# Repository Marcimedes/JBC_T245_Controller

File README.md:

# JBC_T245_Controller
JBC T245 Controller

Mounting Holes:
2.1 mm dia.
64mm x 74mm 

Board:
71mm x 80mm

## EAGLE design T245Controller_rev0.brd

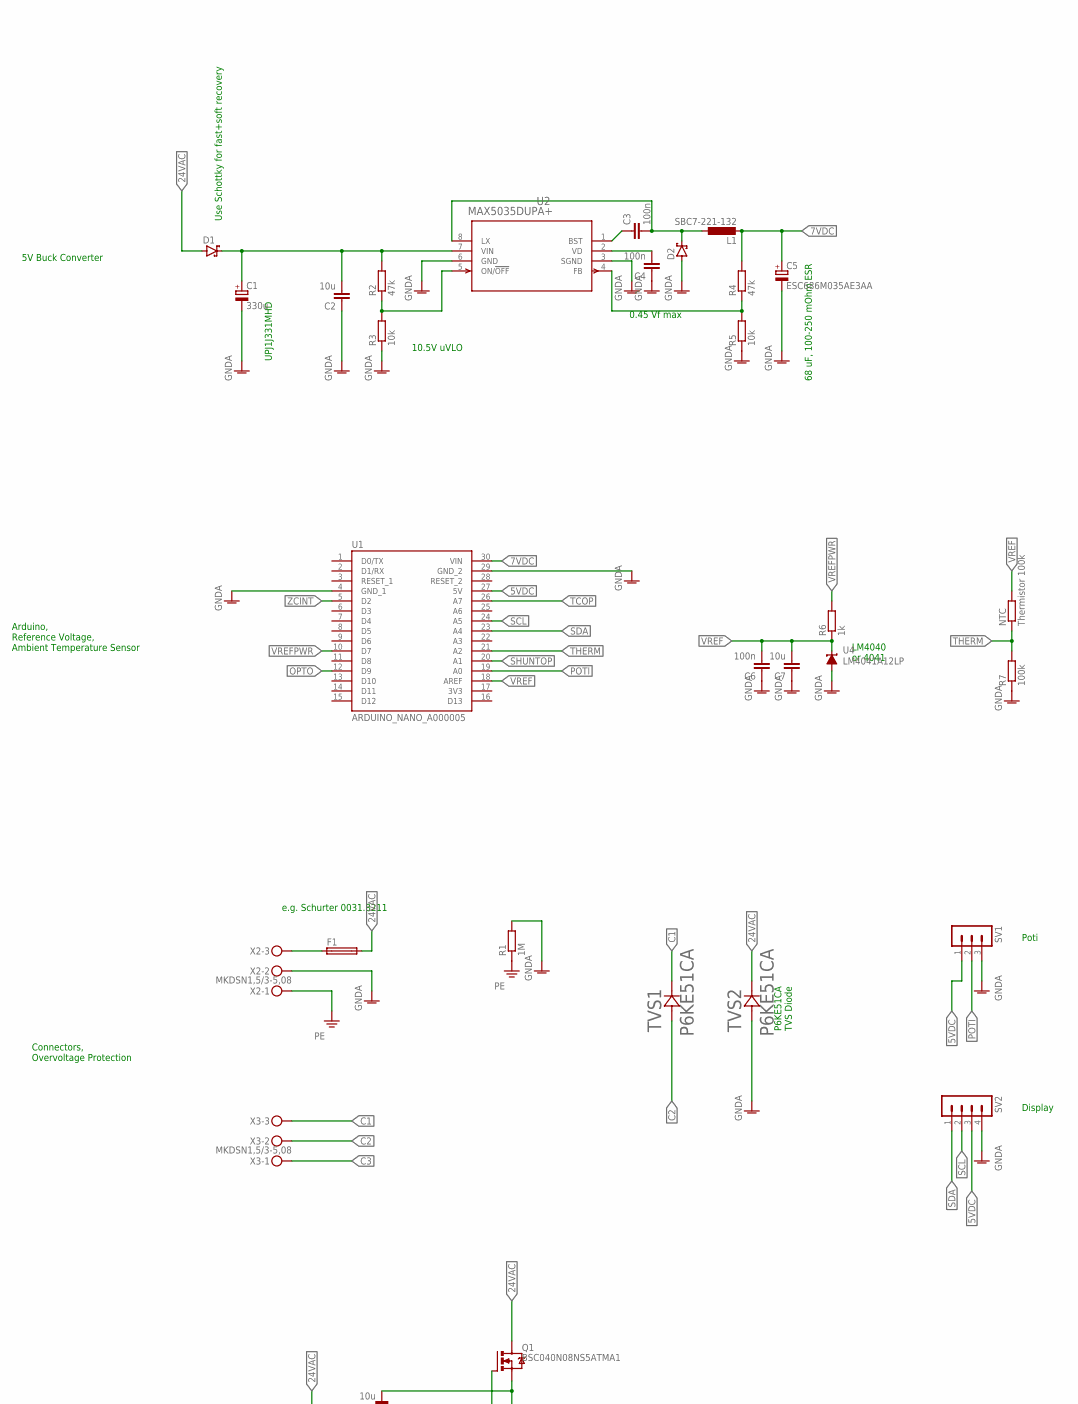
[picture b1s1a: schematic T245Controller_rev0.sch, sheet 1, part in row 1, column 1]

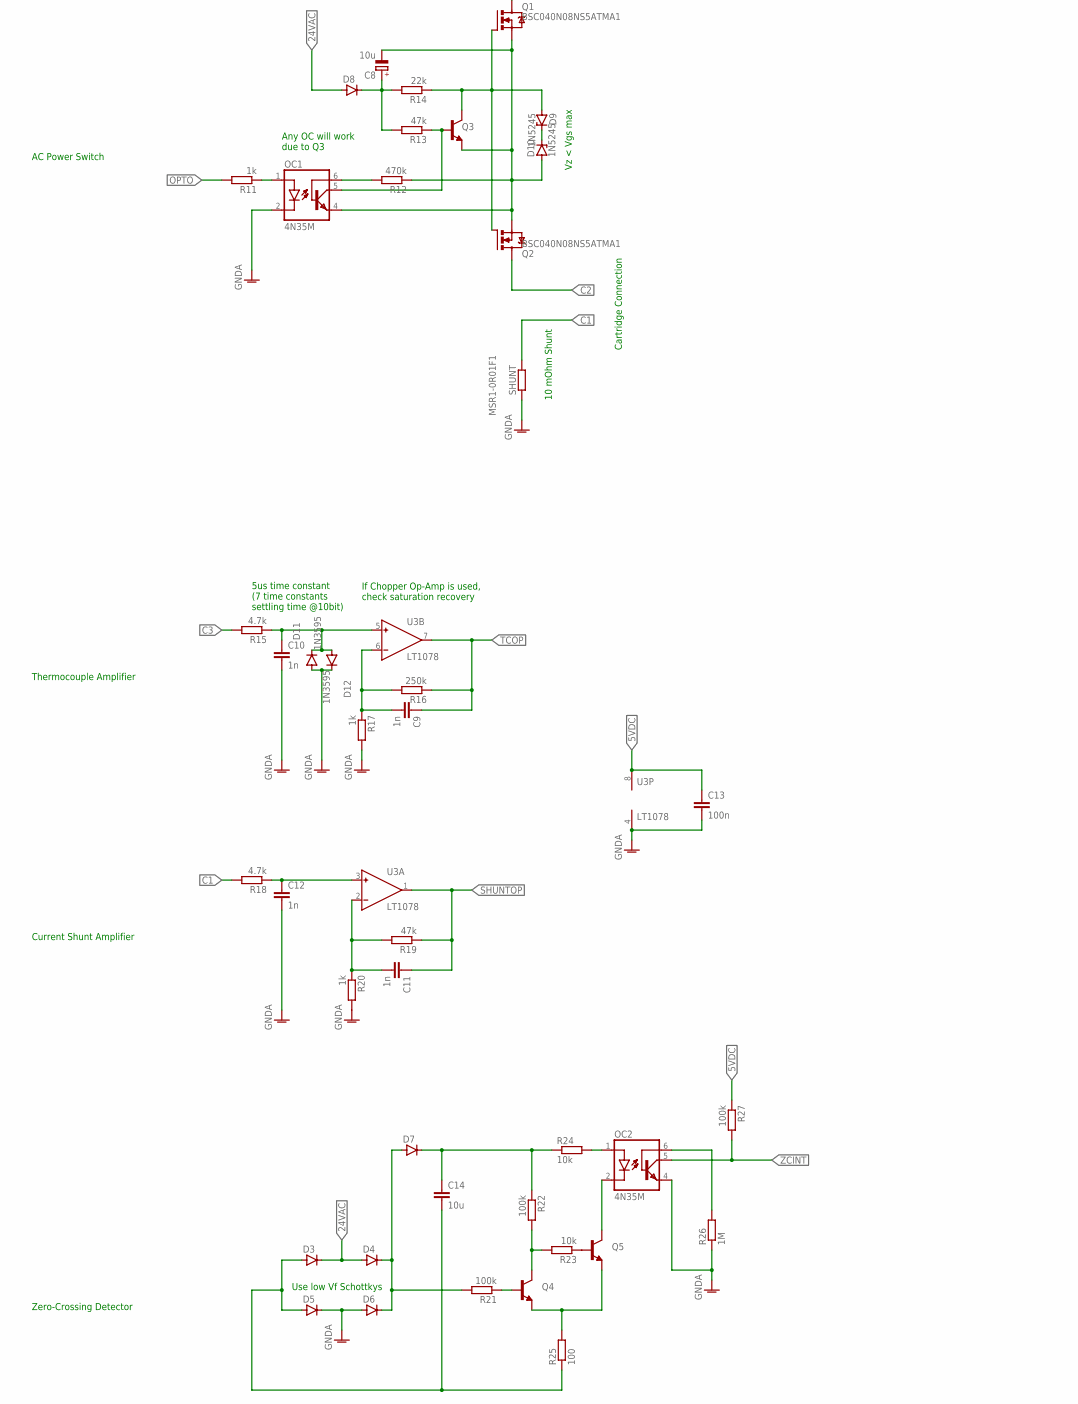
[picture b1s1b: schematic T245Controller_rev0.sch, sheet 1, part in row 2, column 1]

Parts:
C1: 330u; E5-13
C2, C7, C14: 10u; C050-024X044
C3, C4, C6, C13: 100n; C050-024X044
C5: ESC686M035AE3AA; E2,5-6
C8: 10u; E2,5-6
C9, C10, C11, C12: 1n; C050-024X044
D1, D2: SCHOTTKY-DIODEF126Z12; F126Z12
D3, D4, D5, D6, D7, D8: DIODE-D-7.5; D-7.5
D9, D10: 1N5245; DO41Z10
D11, D12: 1N3595; D-7.5
F1: SH22,5A
L1: SBC7-221-132; 0207/10
NTC: Thermistor 100k; 0207/10
OC1, OC2: 4N35M; DIL06
Q1, Q2: BSC040N08NS5ATMA1; TO220BV
Q3, Q4, Q5: 2N5550-NPN-TO92-EBC; TO92-EBC
R1, R26: 1M; 0207/10
R2, R4, R13, R19: 47k; 0207/10
R3, R5, R23, R24: 10k; 0207/10
R6, R11, R17, R20: 1k; 0207/10
R7, R21, R22, R27: 100k; 0207/10
R12: 470k; 0207/10
R14: 22k; 0207/10
R15, R18: 4.7k; 0207/10
R16: 250k; 0207/10
R25: 100; 0207/10
SHUNT: MSR1-0R01F1; 0207/12
SV1: MA03-1
SV2: MA04-1
TVS1, TVS2: P6KE51CA; P6KESERIES_LTF
U1: ARDUINO_NANO_A000005; MODULE_A000005
U2: MAX5035DUPA+; 21-0043_P8+3_MXM
U3: LT1078; DIL08
U4: LM4041A12LP; LP_O-PBCY-W3
X2, X3: MKDSN1,5/3-5,08

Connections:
3V3: U1.17 (3V3)
5VDC: C13.1, R27.1, SV1.1, SV2.3, U1.27 (5V), U3.8 (V+)
7VDC: C5.+, L1.2, R4.2, U1.30 (VIN)
24VAC: D1.A, D3.C, D4.A, D8.A, F1.2, Q1.D, TVS2.1 (11)
C1: R18.2, SHUNT.2, TVS1.1 (11), X3.3
C2: Q2.D, TVS1.2 (12), X3.2
C3: R15.2, X3.1
GNDA: C1.-, C2.1, C4.1, C5.-, C6.1, C7.1, C10.2, C12.2, C13.2, D2.A, D5.C, D6.A, D11.A, D12.C, OC1.2 (C), OC2.4 (EMI), R1.2, R3.1, R5.1, R7.1, R17.2, R20.2, R26.1, SHUNT.1, SV1.3, SV2.4, TVS2.2 (12), U1.4 (GND_1), U1.29 (GND_2), U2.3 (SGND), U2.6 (GND), U3.4 (V-), U4.3 (A), X2.2
unnamed: C9.2, R16.2, R17.1, U3.6 (IN-)
unnamed: OC1.1 (A), R11.1
unnamed: D9.A, Q1.G, Q2.G, Q3.C, R14.1
unnamed: C8.-, D10.A, OC1.4 (EMI), Q1.S, Q2.S, Q3.E, R12.1
unnamed: OC1.6 (BAS), R12.2
unnamed: Q5.B, R23.1
unnamed: R4.1, R5.2, U2.4 (FB)
unnamed: C3.2, D2.C, L1.1, U2.8 (LX)
unnamed: C8.+, D8.C, R13.2, R14.2
unnamed: C1.+, C2.2, D1.C, R2.2, U2.7 (VIN)
unnamed: C10.1, D11.C, D12.A, R15.1, U3.5 (IN+)
unnamed: C3.1, U2.1 (BST)
unnamed: OC1.5 (COL), Q3.B, R13.1
unnamed: D9.C, D10.C
unnamed: R2.1, R3.2, U2.5 (ON/!OFF)
unnamed: C4.2, U2.2 (VD)
unnamed: C14.2, D3.A, D5.A, R25.1
unnamed: OC2.6 (BAS), R26.2
unnamed: F1.1, X2.3
unnamed: C12.1, R18.1, U3.3 (IN+)
unnamed: D4.C, D6.C, D7.A, R21.2
unnamed: C11.2, R19.2, R20.1, U3.2 (IN-)
unnamed: Q4.B, R21.1
unnamed: C14.1, D7.C, R22.1, R24.1
unnamed: Q4.C, R22.2, R23.2
unnamed: Q4.E, Q5.E, R25.2
unnamed: OC2.1 (A), R24.2
unnamed: OC2.2 (C), Q5.C
OPTO: R11.2, U1.12 (D9)
PE: R1.1, X2.1
POTI: SV1.2, U1.19 (A0)
SCL: SV2.2, U1.24 (A5)
SDA: SV2.1, U1.23 (A4)
SHUNTOP: C11.1, R19.1, U1.20 (A1), U3.1 (OUT)
TCOP: C9.1, R16.1, U1.26 (A7), U3.7 (OUT)
THERM: NTC.1, R7.2, U1.21 (A2)
VREF: C6.2, C7.2, NTC.2, R6.1, U1.18 (AREF), U4.2 (C)
VREFPWR: R6.2, U1.10 (D7)
ZCINT: OC2.5 (COL), R27.2, U1.5 (D2)

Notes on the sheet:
Use Schottky for fast+soft recovery
Any OC will work due to Q3
5us time constant (7 time constants settling time @10bit)
Vz < Vgs max
0.45 Vf max
10.5V uVLO
UPJ1J331MHD
68 uF, 100-250 mOhm ESR
e.g. Schurter 0031.8211
LM4040 or 4041
If Chopper Op-Amp is used, check saturation recovery
10 mOhm Shunt
Cartridge Connection
Zero-Crossing Detector
Current Shunt Amplifier
Thermocouple Amplifier
AC Power Switch
Connectors, Overvoltage Protection
Arduino, Reference Voltage, Ambient Temperature Sensor
5V Buck Converter
P6KE51CA TVS Diode
Use low Vf Schottkys
Poti
Display

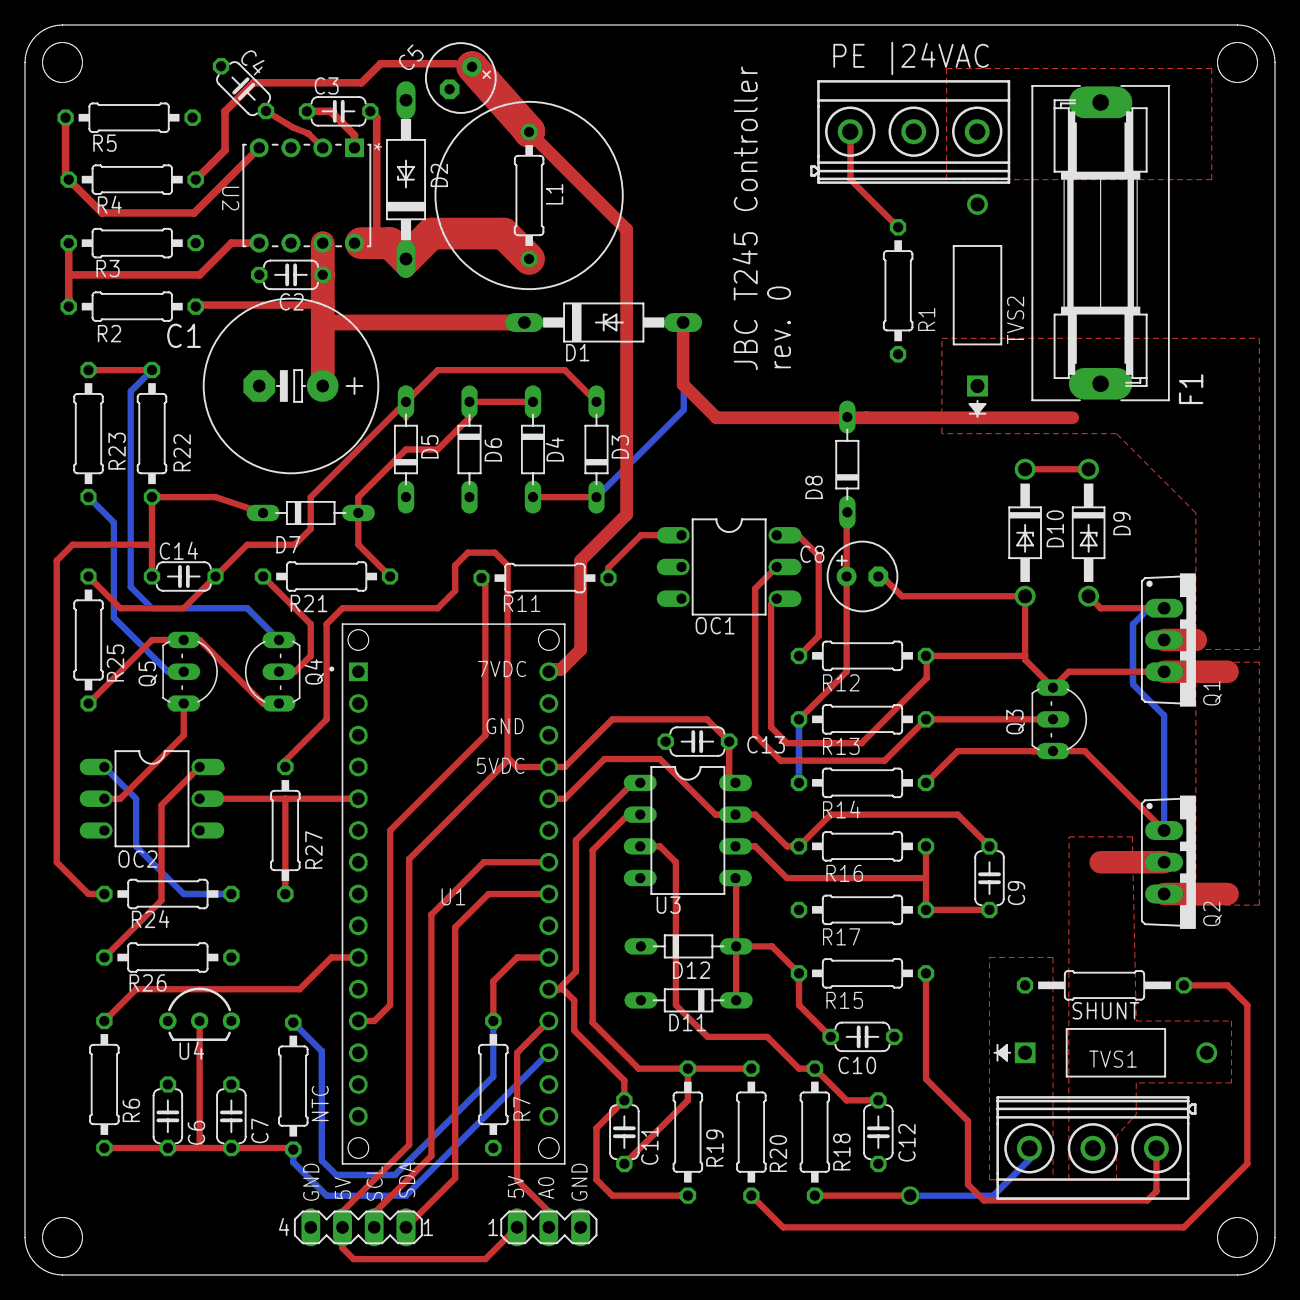
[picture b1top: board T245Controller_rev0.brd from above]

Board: 2 copper layers, 100.0 x 100.0 mm, 71 parts (0 on the bottom side), 46 nets.

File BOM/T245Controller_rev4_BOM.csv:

,T245 (24 VAC),,,
,,,,
Part,Nominal Value,Example Part,Description,Approx. Price
C1,470uF 50V,Nichicon UHE1H471MHD3,"DC-DC input cap, impedance < 80 mOhms @100kHz",1.30 
C2,1uF 100V,FG24X7S2A105KRT06,"DC-DC input cap, MLCC",0.60 
C3,100nF 100V,SR211C104KARTR1,DC-DC cap,0.20 
C4,100nF 100V,SR211C104KARTR1,DC-DC cap,0.20 
C5,68uF 16V,Nichicon UHV1V680MED,"DC-DC output cap, impedance 100-200 mOhms @100kHz",0.40 
C6,100nF 16V,SR211C104KARTR1,Voltage Reference cap,0.20 
C7,10uF 10V,FG14X7R1A106KRT06 ,Voltage Reference cap,0.50 
C8,47uF 50V,Rubycon 50YXJ47M6.3X11,Villard Circuit cap,0.30 
C9,"1nF, 16V",Vishay K102K10X7RH5UH5,Opamp loop cap,0.10 
C10,"1nF, 16V",Vishay K102K10X7RH5UH5,Amplifier input lowpass cap,0.10 
C11,"1nF, 16V",Vishay K102K10X7RH5UH5,Opamp loop cap,0.10 
C12,"1nF, 16V",Vishay K102K10X7RH5UH5,Amplifier input lowpass cap,0.10 
C13,"100nF, 16V",SR211C104KARTR1,Opamp bypass cap,0.20 
C14,"10uF, 25V",FK26X7R1E106K ,DC-DC output filter cap,0.60 
C15,"1uF, 100V",FG24X7S2A105KRT06,DC-DC input filter cap,0.60 
,,,,
D1,1A 100V,1N4007,Rectifier diode,0.20 
D2,60V Schottky,SMC SB560TA,"DC-DC freewheeling diode, <0.45V Vf @2.5A",0.40 
D8,80V,1N3595 ,Villard Circuit diode,0.20 
D9,15V Zener,1N5245,Gate voltage limiting Z-Diode,0.20 
D10,15V Zener,1N5245,Gate voltage limiting Z-Diode,0.20 
D11,,1N3595 ,Thermocouple amplifier clamping diode,0.20 
D12,,1N3595 ,Thermocouple amplifier clamping diode,0.20 
D13,1A 10V,1N4007,Reverse current protection when Arduino is USB-powered,0.20 
,,,,
F1,,,"Fuse holder grid 22,5mm",0.80 
L1,220 uH,SBC7-221-132 ,DC-DC power inductor,1.80 
L2,2.2uH,B78108S1222K000,DC-DC output filter inductor,0.30 
L3,2.2uH,B78108S1222K000,DC-DC input filter cap inductor,0.30 
MOV,47V,Panasonic ERZ-V10D470,"Varistor, 7.5 mm lead spacing",0.30 
,,,,
Q1,60V 15A,STF100N6F7 ,N-channel mosfet <10 mOhm Rds(on) if without heatsink,1.50 
Q2,60V 15A,STF100N6F7 ,N-channel mosfet <10 mOhm Rds(on) if without heatsink,1.50 
Q3,80V PNP,KSA916,PNP Transistor 80V,0.40 
Q4,40V NPN,2N3904,NPN Transistor,0.30 
Q5,40V NPN,2N3904,NPN Transistor,0.30 
Q6,40V PNP,2N3906,PNP Transistor,0.30 
,,,,
NTC,100k,TT7-100KC3-3 ,Thermistor 100k,0.50 
R1,1M,VR37000001004JR500 ,"Impulse resistant, GND to physical earth connection",0.40 
R2,47k,RNF14FTD47K0,1/4W 0207,0.10 
R3,10k,RNMF14FTC10K0,1/4W 0207,0.10 
R4,56k,MF0207FTE52-56K,1/4W 0207,0.10 
R5,10k,RNMF14FTC10K0,1/4W 0207,0.10 
R6,1k,RNF14FTD1K00,1/4W 0207,0.10 
R7,100k,RNMF14FTC100K,1/4W 0207,0.10 
R8,4.7k,MFR50SFTE52-4K7 ,1/4W 0207,0.10 
R9,4.7k,MFR50SFTE52-4K7 ,1/4W 0207,0.10 
R10,1k,RNF14FTD1K00,1/4W 0207,0.10 
R11,1k,RNF14FTD1K00,1/4W 0207,0.10 
R12,470k,MFR50SFTE52-470K ,1/4W 0207,0.10 
R13,47k,RNF14FTD47K0,1/4W 0207,0.10 
R14,1k,RNF14FTD1K00,1/4W 0207,0.10 
R15,4.7k,MFR50SFTE52-4K7 ,1/4W 0207,0.10 
R16,220k,MF0207FTE52-220K ,"1/4W 1% 0207, sets thermocouple amplifier gain",0.10 
R17,1k,RNF14FTD1K00,"1/4W 1% 0207, sets thermocouple amplifier gain",0.10 
R18,4.7k,MFR50SFTE52-4K7 ,1/4W 0207,0.10 
R19,47k,RNF14FTD47K0,"1/4W 1% 0207, sets current sense gain",0.10 
R20,1k,RNF14FTD1K00,"1/4W 1% 0207, sets current sense gain",0.10 
R21,10k,RNMF14FTC10K0,1/4W 0207,0.10 
R22,100k,RNMF14FTC100K,1/4W 0207,0.10 
R23,10k,RNMF14FTC10K0,1/4W 0207,0.10 
R24,100k,RNMF14FTC100K,1/4W 0207,0.10 
R28,1k,RNF14FTD1K00,1/4W 0207,0.10 
,,,,
TVS1,43V,Littelfuse P4KE43CA,"Bidirectional TVS diode, mosfet ESD protection",0.40 
TVS2,7.5V,Littelfuse P4KE7.5CA,"Bidirectional TVS diode, sleep sensor ESD protection",0.50 
,,,,
U1,,ARDUINO NANO A000005,Microcontroller,8.00 
U2,,MAX5035DUPA+,"DC-DC Converter, 76V Vin, 1A Iout",4.10 
U3,,LT1078CN8 ,"Rail-to-rail input Opamp, low offset, input CM includes ground",5.70 
U4,,LM4041A12LP,Shunt voltage reference,0.70 
OC1,,4N35M,"Optocoupler, 6 pin DIP",0.50 
,,,,
X2,,Weidmuller 1760500000,"PCB terminal 5,08 mm pitch",0.70 
X3,,Weidmuller 1760500000,"PCB terminal 5,08 mm pitch",0.70 
,,,,
CONN,,M22-2511005 ,Pin header,0.10 
CONN,,PPPC151LFBN-RC ,Arduino connector,0.40 
FUSE,5A 250V FB,0217005.HXP ,5x20 5A 250V fast blow,0.50 
SHUNT,10 mOhm,MSR1-0R01F1 ,10 mOhm Shunt for current measuring,0.80 
,,,,
,,,,
,,,,41.50 

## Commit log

2022-01-22 Create TOC
2022-01-22 Create test
